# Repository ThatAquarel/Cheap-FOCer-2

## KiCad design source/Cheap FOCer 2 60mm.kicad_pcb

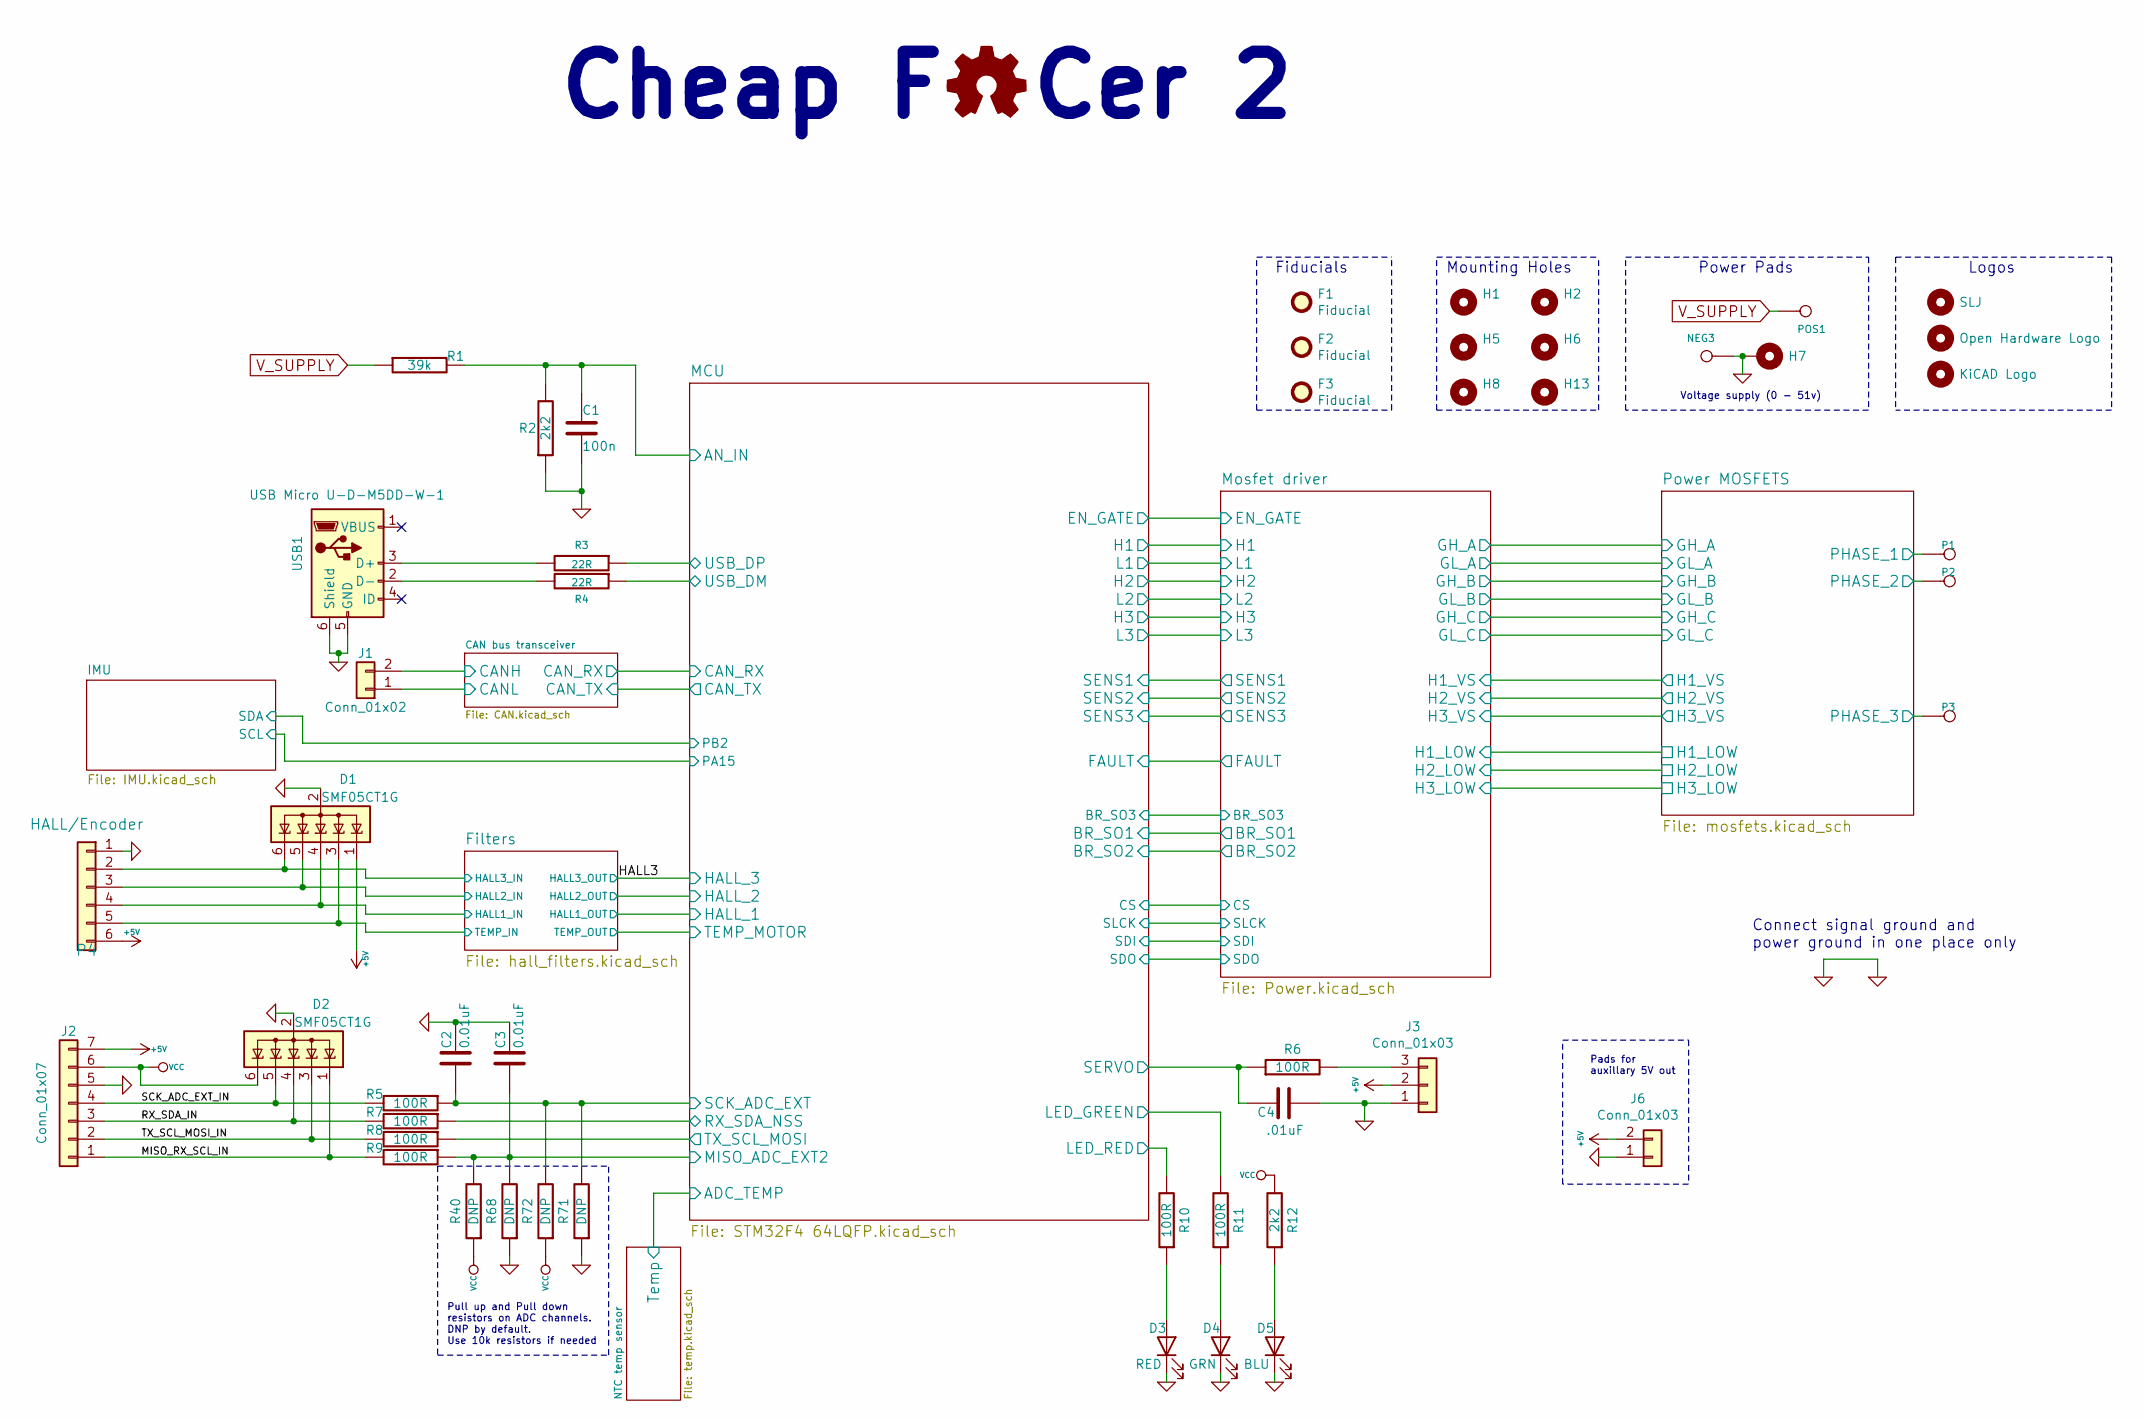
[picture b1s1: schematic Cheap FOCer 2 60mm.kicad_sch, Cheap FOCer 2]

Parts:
C1: 100n; C_0603_1608Metric
C2, C3: 0.01uF; C_0603_1608Metric
C4: .01uF; C_0603_1608Metric
D1, D2: SMF05CT1G; SOT-363_SC-70-6
D3: RED; LED_0603_1608Metric
D4: GRN; LED_0603_1608Metric
D5: BLU; LED_0603_1608Metric
F1, F2, F3: Fiducial; Fiducial_1mm_Dia_2mm_Outer
H1, H2, H5, H6, H7, H8, H13: MountingHole; MountingHole_3.2mm_M3_ISO14580_Pad
H3: SLJ; Sam_J
H4: Open Hardware Logo; OSHW-Logo2_9.8x8mm_SilkScreen
H9: KiCAD Logo; KiCad-Logo2_5mm_SilkScreen
J1: Conn_01x02; JST_PH_B2B-PH-K_1x02_P2.00mm_Vertical
J2: Conn_01x07; JST_PH_B7B-PH-K_1x07_P2.00mm_Vertical
J3: Conn_01x03; JST_PH_B3B-PH-K_1x03_P2.00mm_Vertical
J6: Conn_01x03; PinHeader_1x02_P2.54mm_Vertical
NEG3: MOTOR3; 1pin_4mm
P1, P2, P3: MOTOR1; 1pin_4mm
P4: HALL/Encoder; JST_PH_B6B-PH-K_1x06_P2.00mm_Vertical
POS1: POS; 1pin_4mm
R1: 39k; R_0603_1608Metric
R2, R12: 2k2; R_0603_1608Metric
R3, R4: 22R; R_0603_1608Metric
R5, R6, R7, R8, R9, R10, R11: 100R; R_0603_1608Metric
R40, R68, R71, R72: DNP; R_0603_1608Metric
USB1: USB Micro U-D-M5DD-W-1; USB_Micro-B_Wuerth_614105150721_Vertical

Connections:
+5V: D1.1 (K), J2.7, J3.2, J6.2, P4.6; also elsewhere on the board
/CAN bus transceiver/CANH: J1.2; also elsewhere on the board
/CAN bus transceiver/CANL: J1.1; also elsewhere on the board
/Filters/HALL1_IN: D1.4 (K), P4.4; also elsewhere on the board
/Filters/HALL2_IN: D1.5 (K), P4.3; also elsewhere on the board
/Filters/TEMP_IN: D1.3 (K), P4.5; also elsewhere on the board
/HALL3: D1.6 (K), P4.2; also elsewhere on the board
/MCU/AN_IN: C1.2, R1.2, R2.2; also elsewhere on the board
/MCU/LED_GREEN: R11.2; also elsewhere on the board
/MCU/LED_RED: R10.2; also elsewhere on the board
/MCU/MISO_ADC_EXT2: C3.2, R9.1, R40.2, R68.2; also elsewhere on the board
/MCU/RX_SDA_NSS: R7.1; also elsewhere on the board
/MCU/SCK_ADC_EXT: C2.2, R5.1, R71.2, R72.2; also elsewhere on the board
/MCU/SERVO: C4.2, R6.1; also elsewhere on the board
/MCU/TX_SCL_MOSI: R8.1; also elsewhere on the board
/MCU/USB_DM: R4.1; also elsewhere on the board
/MCU/USB_DP: R3.1; also elsewhere on the board
/MISO_RX_SCL_IN: D2.1 (K), J2.1, R9.2
/Mosfet driver/H1_VS: P1.1; also elsewhere on the board
/Mosfet driver/H2_VS: P2.1; also elsewhere on the board
/Mosfet driver/H3_VS: P3.1; also elsewhere on the board
/RX_SDA_IN: D2.4 (K), J2.3, R7.2
/SCK_ADC_EXT_IN: D2.5 (K), J2.4, R5.2
/TX_SCL_MOSI_IN: D2.3 (K), J2.2, R8.2
GND: C1.1, C2.1, C3.1, C4.1, D1.2 (A), D2.2 (A), D3.1 (K), D4.1 (K), D5.1 (K), H7.1, J2.5, J3.1, J6.1, NEG3.1, P4.1, R2.1, R68.1, R71.1, USB1.5 (GND), USB1.6 (Shield); also elsewhere on the board
unnamed: D3.2 (A), R10.1
unnamed: D4.2 (A), R11.1
unnamed: D5.2 (A), R12.1
unnamed: J3.3, R6.2
unnamed: R3.2, USB1.3 (D+)
unnamed: R4.2, USB1.2 (D-)
V_SUPPLY: POS1.1, R1.1; also elsewhere on the board

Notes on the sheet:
Mounting Holes
Pull up and Pull down resistors on ADC channels. DNP by default. Use 10k resistors if needed
Power Pads
Connect signal ground and power ground in one place only
Pads for auxillary 5V out
Logos
Fiducials
Voltage supply (0 - 51v)
Cheap F Cer 2

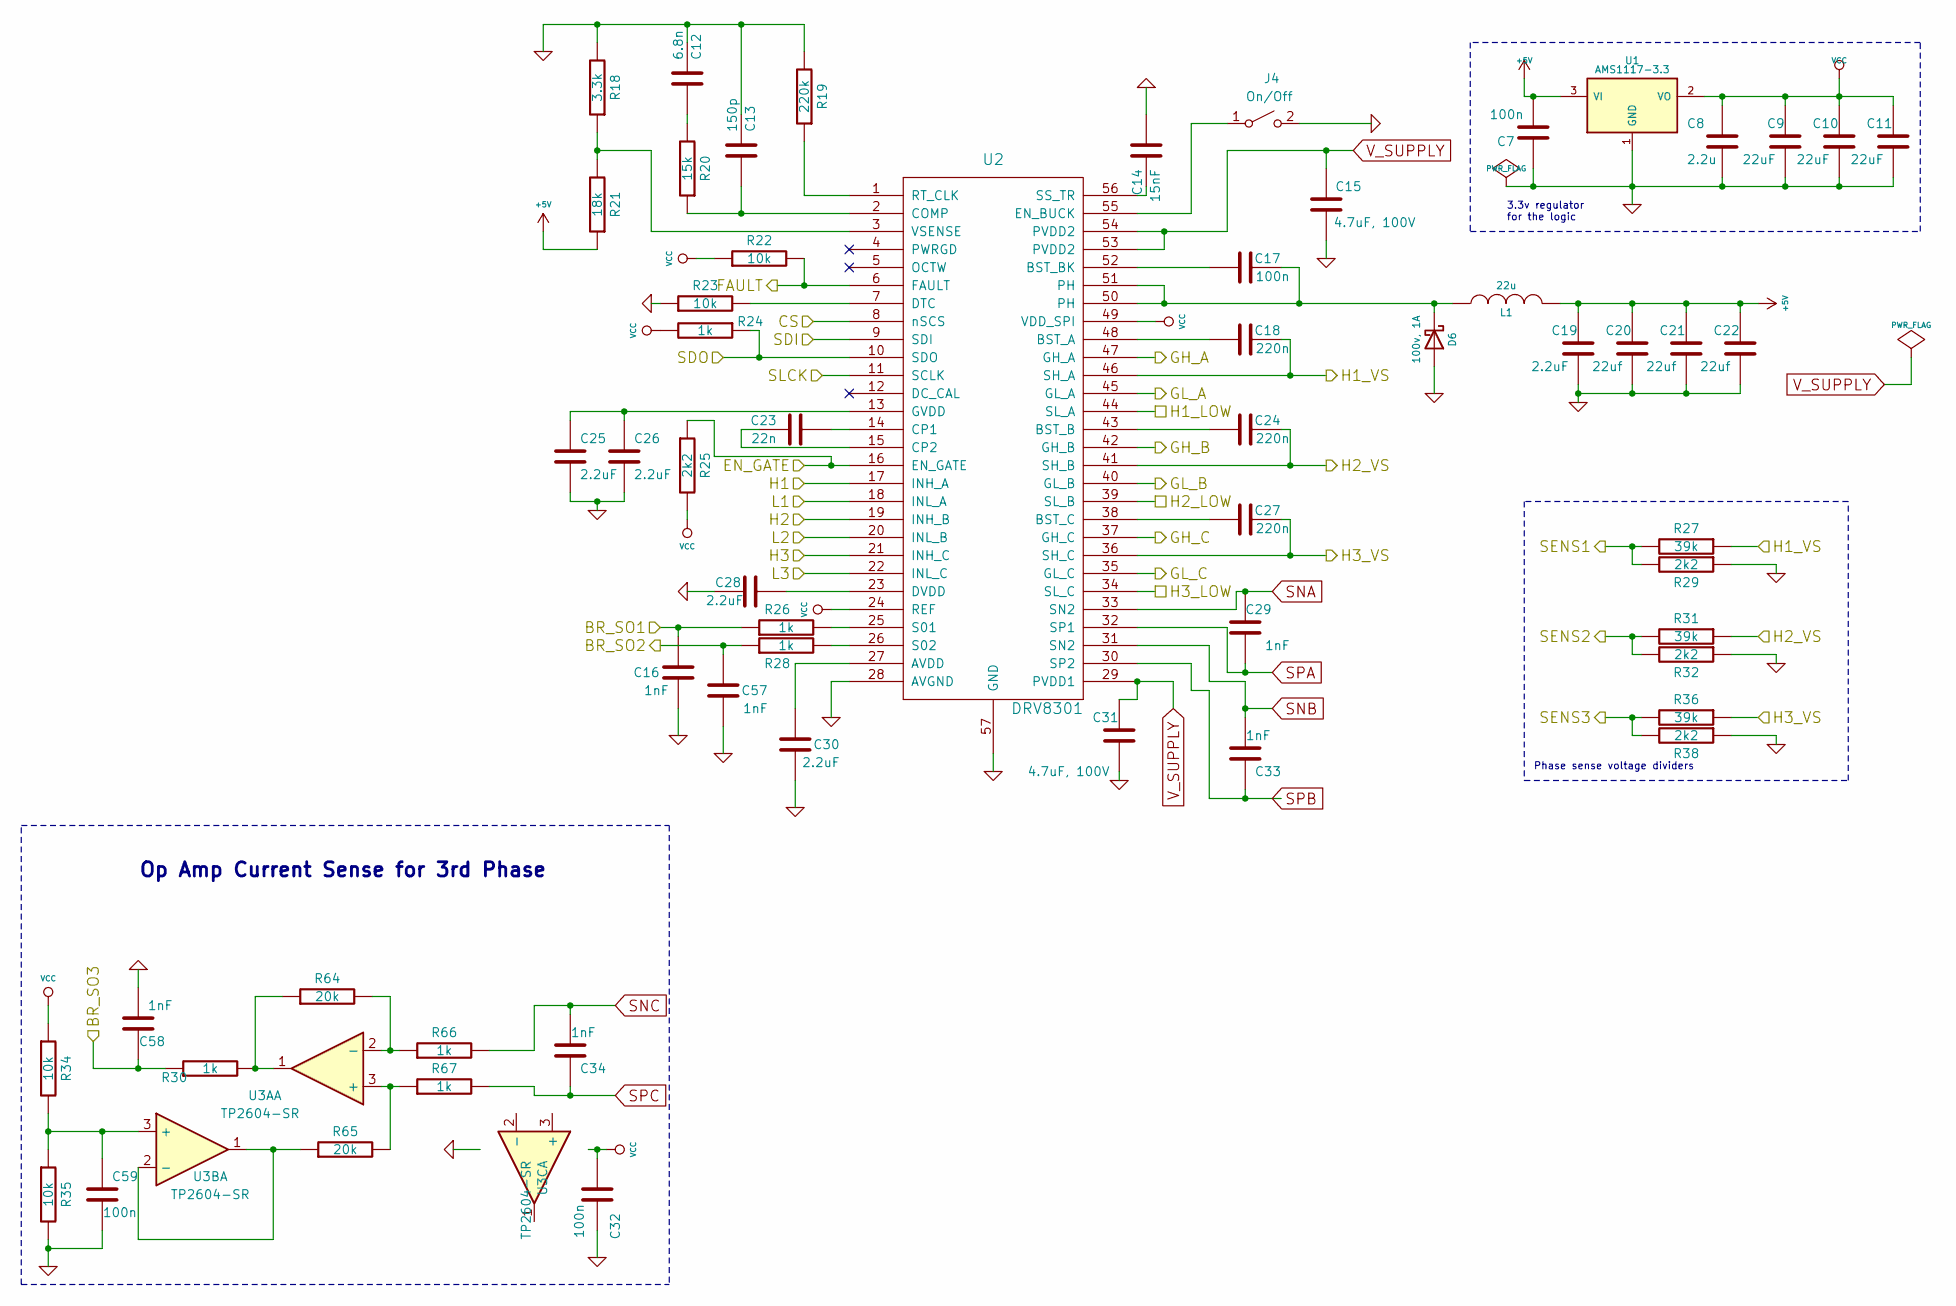
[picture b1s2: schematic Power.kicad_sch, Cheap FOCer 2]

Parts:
C7, C17, C32, C59: 100n; C_0603_1608Metric
C8: 2.2u; C_0603_1608Metric
C9, C10, C11: 22uF; C_0805_2012Metric
C12: 6.8n; C_0603_1608Metric
C13: 150p; C_0603_1608Metric
C14: 15nF; C_0603_1608Metric
C15, C31: 4.7uF, 100V; C_1210_3225Metric
C16, C29, C33, C34, C57, C58: 1nF; C_0603_1608Metric
C18, C24, C27: 220n; C_0603_1608Metric
C19, C25, C26, C28, C30: 2.2uF; C_0603_1608Metric
C20, C21, C22: 22uf; C_0805_2012Metric
C23: 22n; C_0603_1608Metric
D6: 100v, 1A; D_SMA
J4: On/Off; JST_PH_B2B-PH-K_1x02_P2.00mm_Vertical
L1: 22u; L_Taiyo-Yuden_NR-60xx_HandSoldering
R18: 3.3k; R_0603_1608Metric
R19: 220k; R_0603_1608Metric
R20: 15k; R_0603_1608Metric
R21: 18k; R_0603_1608Metric
R22, R23, R34, R35: 10k; R_0603_1608Metric
R24, R26, R28, R30, R66, R67: 1k; R_0603_1608Metric
R25, R29, R32, R38: 2k2; R_0603_1608Metric
R27, R31, R36: 39k; R_0603_1608Metric
R64, R65: 20k; R_0603_1608Metric
U1: AMS1117-3.3; SOT-223-3_TabPin2
U2: DRV8301; HTSSOP-56-1EP_6.1x14mm_P0.5mm_EP3.61x6.35mm
U3A, U3B, U3C: TP2604-SR; SOIC-8_3.9x4.9mm_P1.27mm

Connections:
+5V: C7.2, C19.2, C20.2, C21.2, C22.2, L1.2, R21.1, U1.3 (VI); also elsewhere on the board
/MCU/BR_SO1: C16.2, R26.1; also elsewhere on the board
/MCU/BR_SO2: C57.2, R28.1; also elsewhere on the board
/MCU/BR_SO3: C58.2, R30.1; also elsewhere on the board
/MCU/CS: U2.8 (nSCS); also elsewhere on the board
/MCU/EN_GATE: R25.1, U2.16 (EN_GATE); also elsewhere on the board
/MCU/FAULT: R22.2, U2.6 (FAULT); also elsewhere on the board
/MCU/H1: U2.17 (INH_A); also elsewhere on the board
/MCU/H2: U2.19 (INH_B); also elsewhere on the board
/MCU/H3: U2.21 (INH_C); also elsewhere on the board
/MCU/L1: U2.18 (INL_A); also elsewhere on the board
/MCU/L2: U2.20 (INL_B); also elsewhere on the board
/MCU/L3: U2.22 (INL_C); also elsewhere on the board
/MCU/SDI: U2.9 (SDI); also elsewhere on the board
/MCU/SDO: R24.1, U2.10 (SDO); also elsewhere on the board
/MCU/SENS1: R27.2, R29.2; also elsewhere on the board
/MCU/SENS2: R31.2, R32.2; also elsewhere on the board
/MCU/SENS3: R36.2, R38.2; also elsewhere on the board
/MCU/SLCK: U2.11 (SCLK); also elsewhere on the board
/Mosfet driver/GH_A: U2.47 (GH_A); also elsewhere on the board
/Mosfet driver/GH_B: U2.42 (GH_B); also elsewhere on the board
/Mosfet driver/GH_C: U2.37 (GH_C); also elsewhere on the board
/Mosfet driver/GL_A: U2.45 (GL_A); also elsewhere on the board
/Mosfet driver/GL_B: U2.40 (GL_B); also elsewhere on the board
/Mosfet driver/H1_VS: C18.2, R27.1, U2.46 (SH_A); also elsewhere on the board
/Mosfet driver/H2_LOW: U2.39 (SL_B); also elsewhere on the board
/Mosfet driver/H2_VS: C24.2, R31.1, U2.41 (SH_B); also elsewhere on the board
/Mosfet driver/H3_LOW: U2.34 (SL_C); also elsewhere on the board
/Mosfet driver/H3_VS: C27.2, R36.1, U2.36 (SH_C); also elsewhere on the board
GND: C7.1, C8.2, C9.1, C10.1, C11.1, C12.1, C13.1, C14.2, C15.1, C16.1, C19.1, C20.1, C21.1, C22.1, C25.2, C26.2, C28.2, C30.1, C31.1, C32.1, C57.1, C58.1, C59.2, D6.2 (A), J4.2 (B), R18.2, R19.2, R23.1, R29.1, R32.1, R35.2, R38.1, U1.1 (GND), U2.28 (AVGND), U2.57 (GND); also elsewhere on the board
unnamed: C12.2, R20.2
unnamed: C13.2, R20.1, U2.2 (COMP)
unnamed: C14.1, U2.56 (SS_TR)
unnamed: C17.1, U2.52 (BST_BK)
unnamed: C17.2, D6.1 (K), L1.1, U2.50 (PH), U2.51 (PH)
unnamed: C18.1, U2.48 (BST_A)
unnamed: C23.1, U2.15 (CP2)
unnamed: C23.2, U2.14 (CP1)
unnamed: C24.1, U2.43 (BST_B)
unnamed: C25.1, C26.1, U2.13 (GVDD)
unnamed: C27.1, U2.38 (BST_C)
unnamed: C28.1, U2.23 (DVDD)
unnamed: C30.2, U2.27 (AVDD)
unnamed 75: C59.1, R34.2, R35.1, U3B.3 (+); also elsewhere on the board
unnamed: J4.1 (A), U2.55 (EN_BUCK)
unnamed: R18.1, R21.2, U2.3 (VSENSE)
unnamed: R19.1, U2.1 (RT_CLK)
unnamed: R23.2, U2.7 (DTC)
unnamed: R26.2, U2.25 (S01)
unnamed: R28.2, U2.26 (S02)
unnamed 92: R30.2, R64.1, U3A.1; also elsewhere on the board
unnamed 93: R64.2, R66.1, U3A.2 (-); also elsewhere on the board
unnamed 94: R65.1, U3B.1, U3B.2 (-); also elsewhere on the board
unnamed 95: R65.2, R67.1, U3A.3 (+); also elsewhere on the board
SNA: C29.2, U2.33 (SN2); also elsewhere on the board
SNB: C33.1, U2.31 (SN2); also elsewhere on the board
SNC: C34.1, R66.2; also elsewhere on the board
SPA: C29.1, U2.32 (SP1); also elsewhere on the board
SPB: C33.2, U2.30 (SP2); also elsewhere on the board
SPC: C34.2, R67.2; also elsewhere on the board
V_SUPPLY: C15.2, C31.2, U2.29 (PVDD1), U2.53 (PVDD2), U2.54 (PVDD2); also elsewhere on the board

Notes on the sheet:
Phase sense voltage dividers
3.3v regulator for the logic
Op Amp Current Sense for 3rd Phase

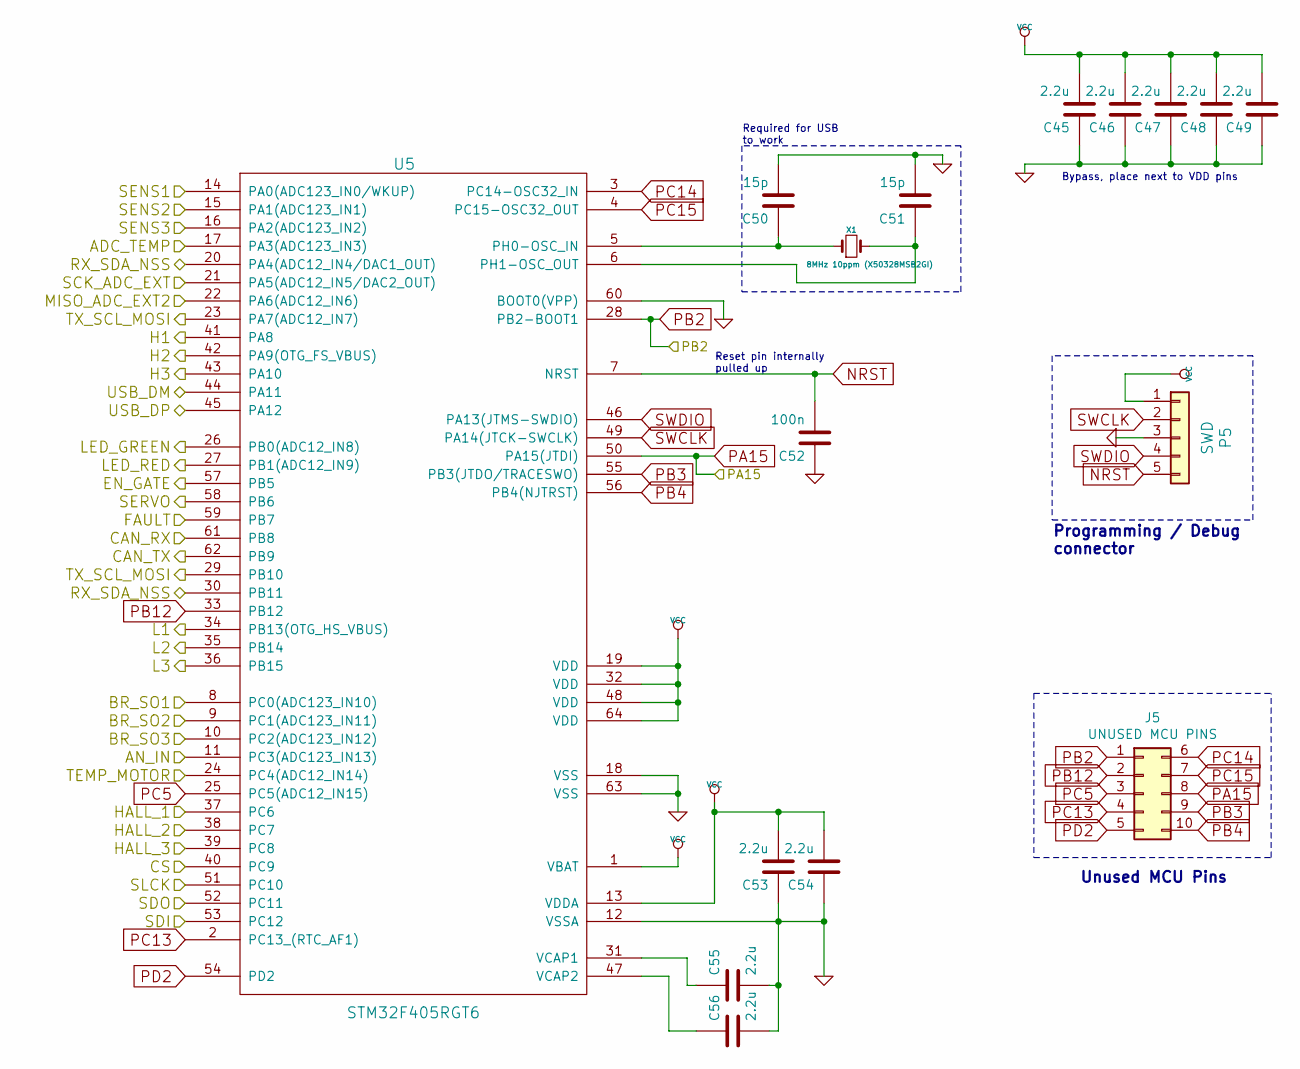
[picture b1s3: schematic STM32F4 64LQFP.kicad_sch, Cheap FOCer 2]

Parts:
C45, C46, C47, C48, C49, C53, C54, C55, C56: 2.2u; C_0603_1608Metric
C50, C51: 15p; C_0603_1608Metric
C52: 100n; C_0603_1608Metric
J5: UNUSED MCU PINS; PinHeader_2x05_P2.00mm_Vertical
P5: SWD; PinHeader_1x05_P2.54mm_Vertical
U5: STM32F405RGT6; LQFP-64_10x10mm_P0.5mm
X1: 8MHz 10ppm (X50328MSB2GI); Crystal_SMD_5032-2Pin_5.0x3.2mm; mfg# ABM3B-8.0-10-1UT

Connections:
/CAN bus transceiver/CAN_RX: U5.61 (PB8); also elsewhere on the board
/CAN bus transceiver/CAN_TX: U5.62 (PB9); also elsewhere on the board
/Filters/HALL1_IN: U5.37 (PC6); also elsewhere on the board
/Filters/HALL2_IN: U5.38 (PC7); also elsewhere on the board
/Filters/TEMP_IN: U5.24 (PC4(ADC12_IN14)); also elsewhere on the board
/HALL3: U5.39 (PC8); also elsewhere on the board
/MCU/ADC_TEMP: U5.17 (PA3(ADC123_IN3)); also elsewhere on the board
/MCU/AN_IN: U5.11 (PC3(ADC123_IN13)); also elsewhere on the board
/MCU/BR_SO1: U5.8 (PC0(ADC123_IN10)); also elsewhere on the board
/MCU/BR_SO2: U5.9 (PC1(ADC123_IN11)); also elsewhere on the board
/MCU/BR_SO3: U5.10 (PC2(ADC123_IN12)); also elsewhere on the board
/MCU/CS: U5.40 (PC9); also elsewhere on the board
/MCU/EN_GATE: U5.57 (PB5); also elsewhere on the board
/MCU/FAULT: U5.59 (PB7); also elsewhere on the board
/MCU/H1: U5.41 (PA8); also elsewhere on the board
/MCU/H2: U5.42 (PA9(OTG_FS_VBUS)); also elsewhere on the board
/MCU/H3: U5.43 (PA10); also elsewhere on the board
/MCU/L1: U5.34 (PB13(OTG_HS_VBUS)); also elsewhere on the board
/MCU/L2: U5.35 (PB14); also elsewhere on the board
/MCU/L3: U5.36 (PB15); also elsewhere on the board
/MCU/LED_GREEN: U5.26 (PB0(ADC12_IN8)); also elsewhere on the board
/MCU/LED_RED: U5.27 (PB1(ADC12_IN9)); also elsewhere on the board
/MCU/MISO_ADC_EXT2: U5.22 (PA6(ADC12_IN6)); also elsewhere on the board
/MCU/RX_SDA_NSS: U5.20 (PA4(ADC12_IN4/DAC1_OUT)), U5.30 (PB11); also elsewhere on the board
/MCU/SCK_ADC_EXT: U5.21 (PA5(ADC12_IN5/DAC2_OUT)); also elsewhere on the board
/MCU/SDI: U5.53 (PC12); also elsewhere on the board
/MCU/SDO: U5.52 (PC11); also elsewhere on the board
/MCU/SENS1: U5.14 (PA0(ADC123_IN0/WKUP)); also elsewhere on the board
/MCU/SENS2: U5.15 (PA1(ADC123_IN1)); also elsewhere on the board
/MCU/SENS3: U5.16 (PA2(ADC123_IN2)); also elsewhere on the board
/MCU/SERVO: U5.58 (PB6); also elsewhere on the board
/MCU/SLCK: U5.51 (PC10); also elsewhere on the board
/MCU/TX_SCL_MOSI: U5.23 (PA7(ADC12_IN7)), U5.29 (PB10); also elsewhere on the board
/MCU/USB_DM: U5.44 (PA11); also elsewhere on the board
/MCU/USB_DP: U5.45 (PA12); also elsewhere on the board
GND: C45.1, C46.1, C47.1, C48.1, C49.1, C50.2, C51.2, C52.1, C53.1, C54.1, C55.2, C56.2, P5.3, U5.12 (VSSA), U5.18 (VSS), U5.60 (BOOT0(VPP)), U5.63 (VSS); also elsewhere on the board
NRST: C52.2, P5.5, U5.7 (NRST)
unnamed: C50.1, U5.5 (PH0-OSC_IN), X1.1
unnamed: C51.1, U5.6 (PH1-OSC_OUT), X1.2
unnamed: C55.1, U5.31 (VCAP1)
unnamed: C56.1, U5.47 (VCAP2)
PB3: J5.9, U5.55 (PB3(JTDO/TRACESWO))
PB4: J5.10, U5.56 (PB4(NJTRST))
PB12: J5.2, U5.33 (PB12)
PC5: J5.3, U5.25 (PC5(ADC12_IN15))
PC13: J5.4, U5.2 (PC13_(RTC_AF1))
PC14: J5.6, U5.3 (PC14-OSC32_IN)
PC15: J5.7, U5.4 (PC15-OSC32_OUT)
PD2: J5.5, U5.54 (PD2)
SWCLK: P5.2, U5.49 (PA14(JTCK-SWCLK))
SWDIO: P5.4, U5.46 (PA13(JTMS-SWDIO))

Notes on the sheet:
Bypass, place next to VDD pins
Programming / Debug connector
Reset pin internally pulled up
Unused MCU Pins
Required for USB to work

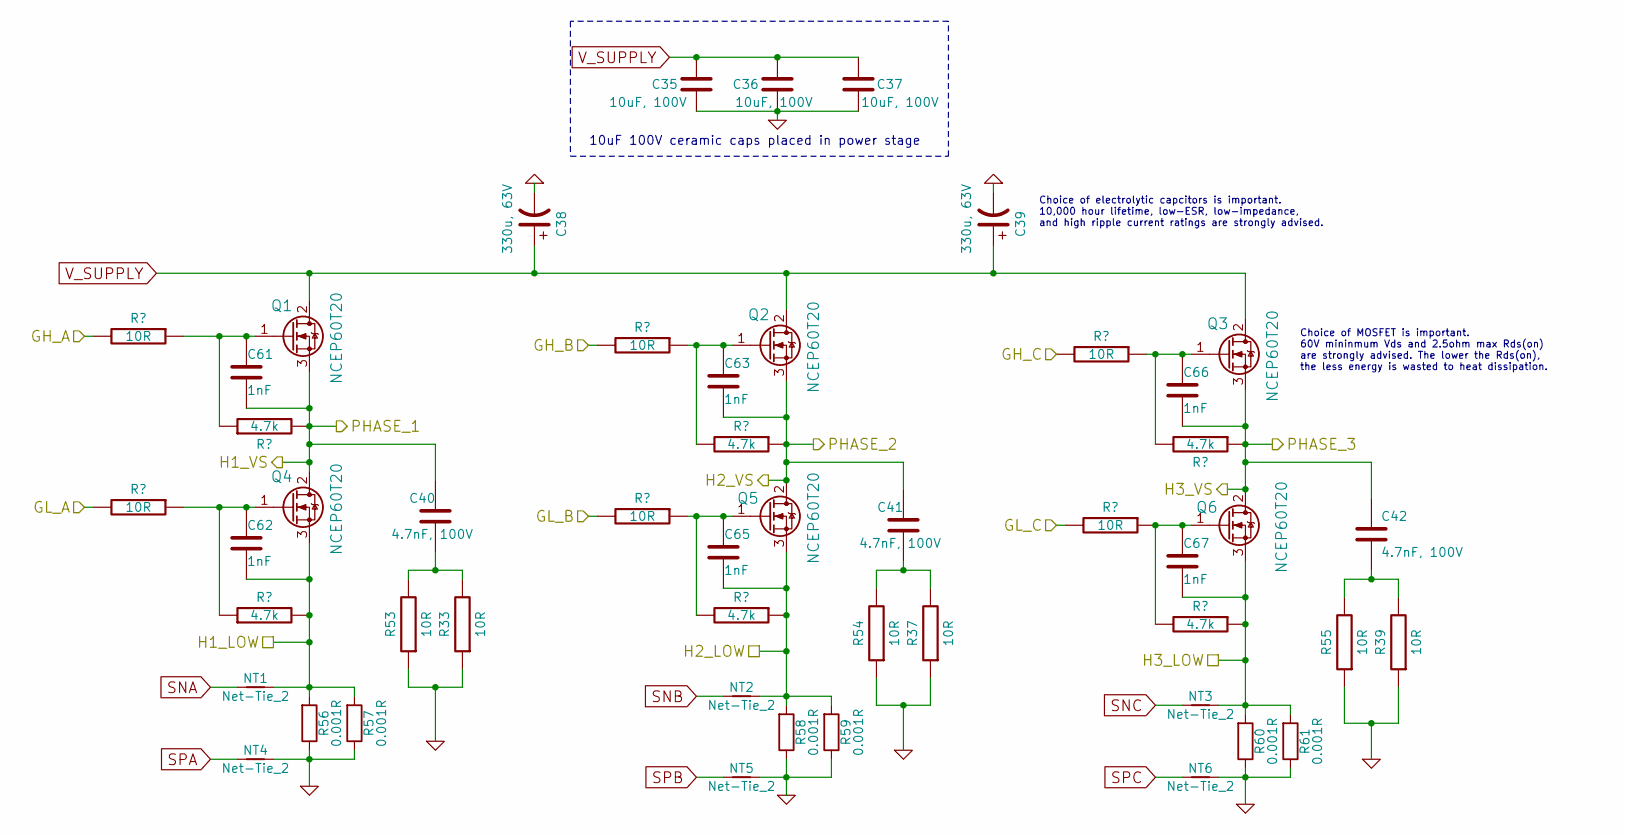
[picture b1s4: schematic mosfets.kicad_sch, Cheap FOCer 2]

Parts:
C35, C36, C37: 10uF, 100V; C_2220_5650Metric_Pad1.97x5.40mm_HandSolder
C38, C39: 330u, 63V; CP_10x20mm_hor_with_model_brd_edge
C40, C41, C42: 4.7nF, 100V; C_0805_2012Metric
C61, C62, C63, C65, C66, C67: 1nF; C_0603_1608Metric
NT1, NT2, NT3, NT4, NT5, NT6: Net-Tie_2; NetTie-2_SMD_Pad0.5mm
Q1, Q2, Q3, Q4, Q5, Q6: NCEP60T20; TO-220-3_Horizontal_TabUp_no_hole
R33, R37, R39, R41, R42, R43, R47, R48, R49, R53, R54, R55: 10R; R_0805_2012Metric
R44, R45, R46, R50, R51, R52: 4.7k; R_0603_1608Metric
R56, R57, R58, R59, R60, R61: 0.001R; R_2512_Yageo_big_pads

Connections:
/Mosfet driver/GH_A: R41.2; also elsewhere on the board
/Mosfet driver/GH_B: R42.2; also elsewhere on the board
/Mosfet driver/GH_C: R43.2; also elsewhere on the board
/Mosfet driver/GL_A: R47.2; also elsewhere on the board
/Mosfet driver/GL_B: R48.2; also elsewhere on the board
/Mosfet driver/H1_VS: C40.1, C61.2, Q1.3 (S), Q4.2 (D), R44.2; also elsewhere on the board
/Mosfet driver/H2_LOW: C65.2, NT2.2, Q5.3 (S), R51.1, R58.2, R59.2; also elsewhere on the board
/Mosfet driver/H2_VS: C41.1, C63.2, Q2.3 (S), Q5.2 (D), R45.1; also elsewhere on the board
/Mosfet driver/H3_LOW: C67.2, NT3.2, Q6.3 (S), R52.1, R60.2, R61.2; also elsewhere on the board
/Mosfet driver/H3_VS: C42.1, C66.2, Q3.3 (S), Q6.2 (D), R46.1; also elsewhere on the board
GND: C35.1, C36.1, C37.1, C38.2, C39.2, NT4.2, NT5.2, NT6.2, R33.1, R37.1, R39.1, R53.1, R54.1, R55.1, R56.1, R57.1, R58.1, R59.1, R60.1, R61.1; also elsewhere on the board
unnamed: C40.2, R33.2, R53.2
unnamed: C41.2, R37.2, R54.2
unnamed: C42.2, R39.2, R55.2
unnamed: C61.1, Q1.1 (G), R41.1, R44.1
unnamed: C63.1, Q2.1 (G), R42.1, R45.2
unnamed: C65.1, Q5.1 (G), R48.1, R51.2
unnamed: C66.1, Q3.1 (G), R43.1, R46.2
SNA: NT1.1; also elsewhere on the board
SNB: NT2.1; also elsewhere on the board
SNC: NT3.1; also elsewhere on the board
SPA: NT4.1; also elsewhere on the board
SPB: NT5.1; also elsewhere on the board
SPC: NT6.1; also elsewhere on the board
V_SUPPLY: C35.2, C36.2, C37.2, C38.1, C39.1, Q1.2 (D), Q2.2 (D), Q3.2 (D); also elsewhere on the board

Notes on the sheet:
10uF 100V ceramic caps placed in power stage
Choice of MOSFET is important. 60V mininmum Vds and 2.5ohm max Rds(on) are strongly advised. The lower the Rds(on), the less energy is wasted to heat dissipation.
Choice of electrolytic capcitors is important. 10,000 hour lifetime, low-ESR, low-impedance, and high ripple current ratings are strongly advised.

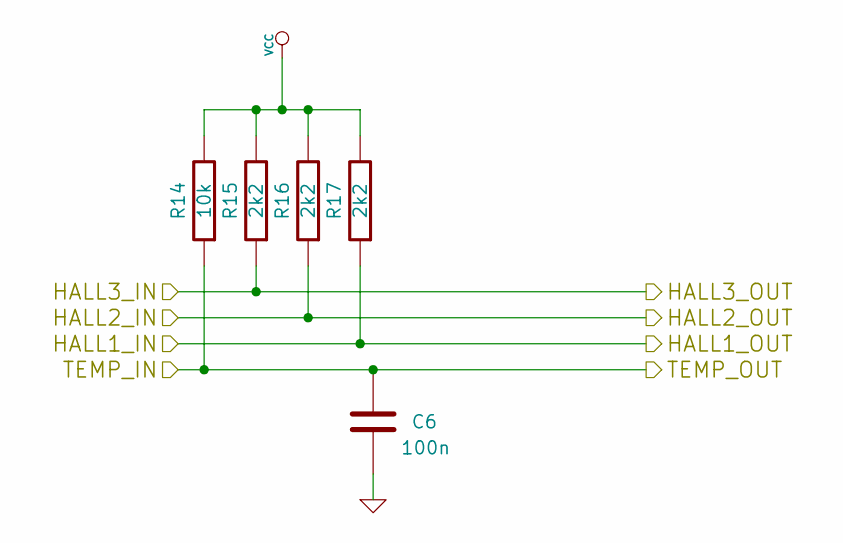
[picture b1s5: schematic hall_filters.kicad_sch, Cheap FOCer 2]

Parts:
C6: 100n; C_0603_1608Metric
R14: 10k; R_0603_1608Metric
R15, R16, R17: 2k2; R_0603_1608Metric

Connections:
/Filters/HALL1_IN: R17.1; also elsewhere on the board
/Filters/HALL2_IN: R16.1; also elsewhere on the board
/Filters/TEMP_IN: C6.2, R14.1; also elsewhere on the board
/HALL3: R15.1; also elsewhere on the board
GND: C6.1; also elsewhere on the board

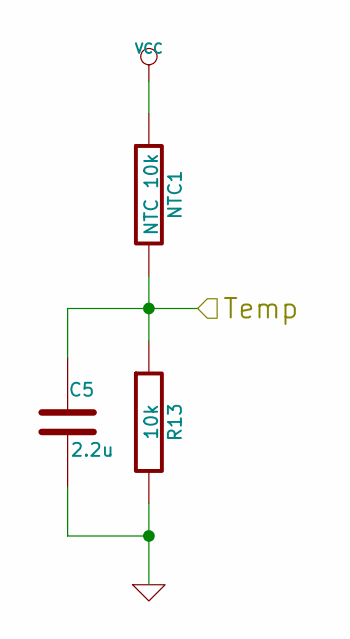
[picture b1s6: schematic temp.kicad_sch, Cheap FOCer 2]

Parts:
C5: 2.2u; C_0603_1608Metric
NTC1: NTC 10k; R_0603_1608Metric
R13: 10k; R_0603_1608Metric

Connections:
/MCU/ADC_TEMP: C5.1, NTC1.2, R13.1; also elsewhere on the board
GND: C5.2, R13.2; also elsewhere on the board

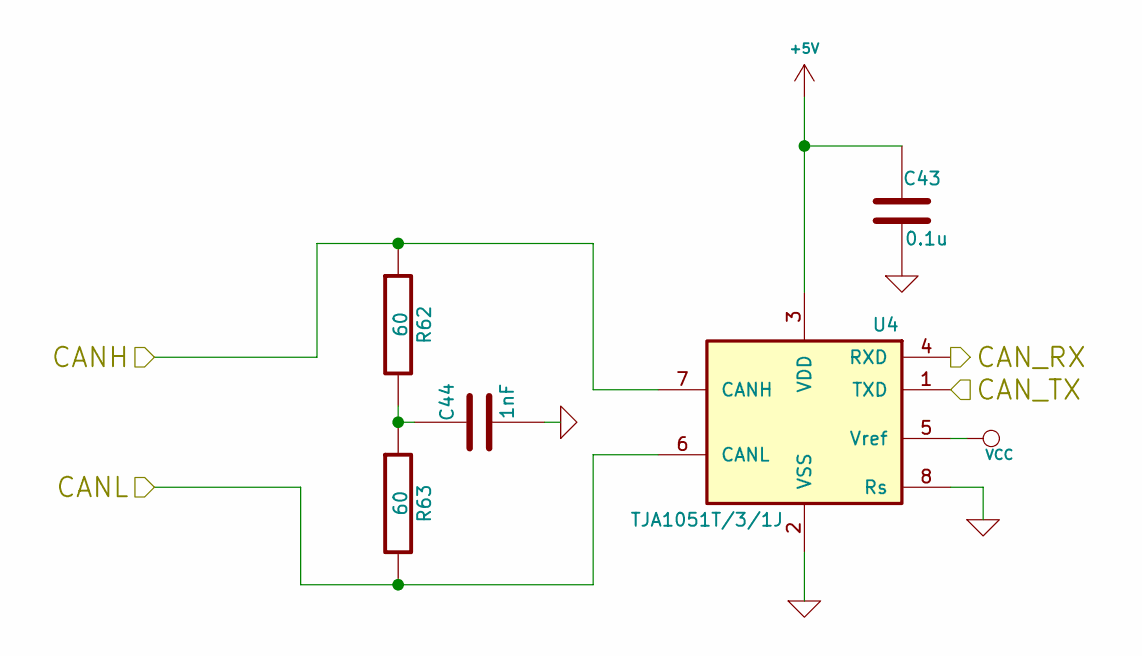
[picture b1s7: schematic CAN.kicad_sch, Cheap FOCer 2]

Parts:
C43: 0.1u; C_0603_1608Metric
C44: 1nF; C_0603_1608Metric
R62, R63: 60; R_0603_1608Metric
U4: TJA1051T/3/1J; SOIC-8_3.9x4.9mm_P1.27mm

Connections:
+5V: C43.1, U4.3 (VDD); also elsewhere on the board
/CAN bus transceiver/CANH: R62.1, U4.7 (CANH); also elsewhere on the board
/CAN bus transceiver/CANL: R63.2, U4.6 (CANL); also elsewhere on the board
/CAN bus transceiver/CAN_RX: U4.4 (RXD); also elsewhere on the board
/CAN bus transceiver/CAN_TX: U4.1 (TXD); also elsewhere on the board
GND: C43.2, C44.2, U4.2 (VSS), U4.8 (Rs); also elsewhere on the board
unnamed: C44.1, R62.2, R63.1

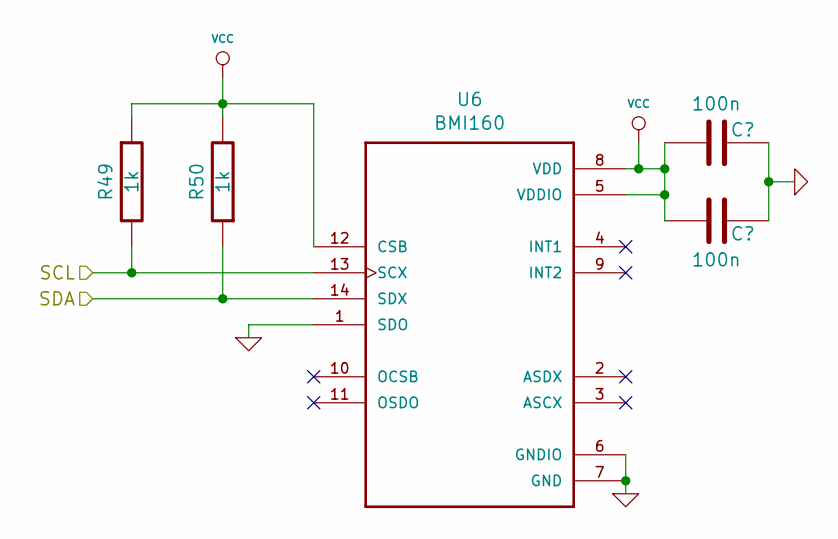
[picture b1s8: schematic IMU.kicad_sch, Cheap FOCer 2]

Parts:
C60, C64: 100n; C_0603_1608Metric
R49, R50: 1k; R_0603_1608Metric
U6: BMI160; Bosch_LGA-14_3x2.5mm_P0.5mm

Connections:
GND: C60.1, C64.1, U6.1 (SDO), U6.6 (GNDIO), U6.7 (GND); also elsewhere on the board

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
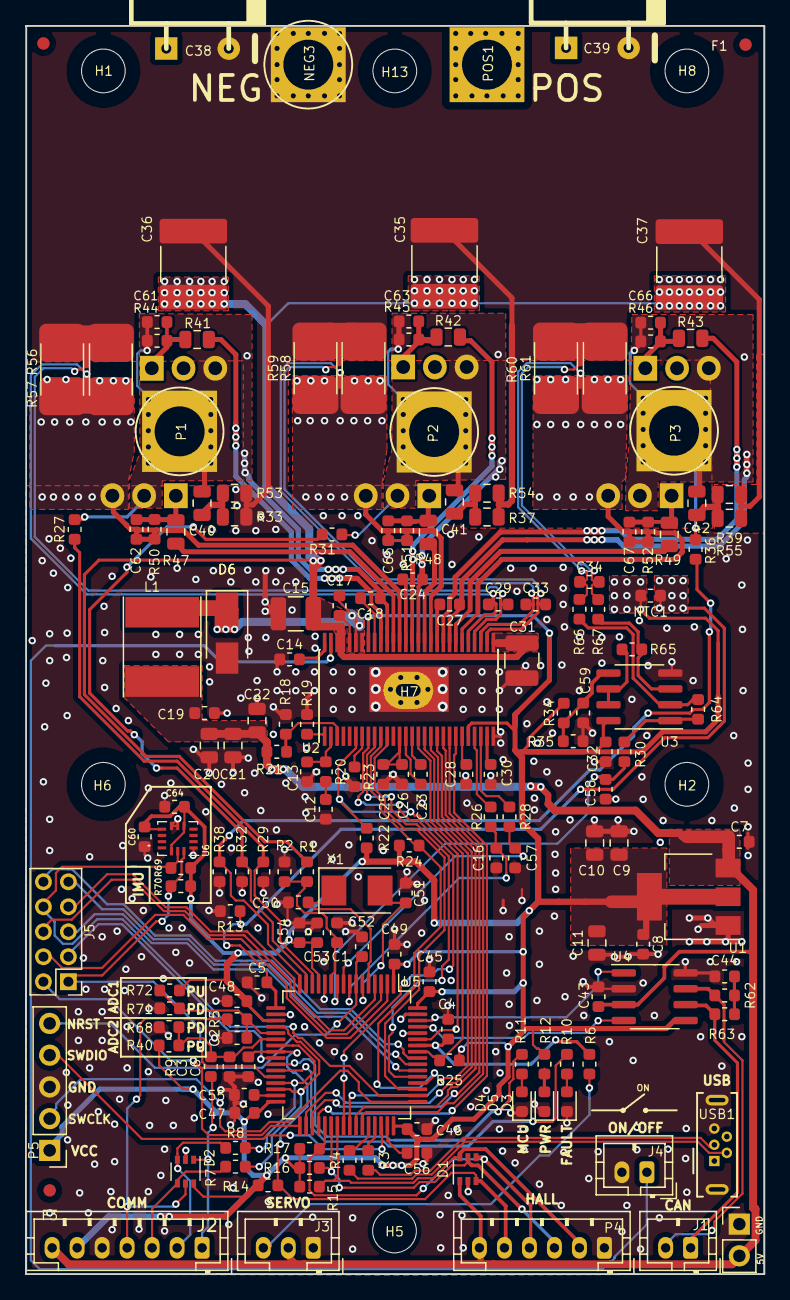
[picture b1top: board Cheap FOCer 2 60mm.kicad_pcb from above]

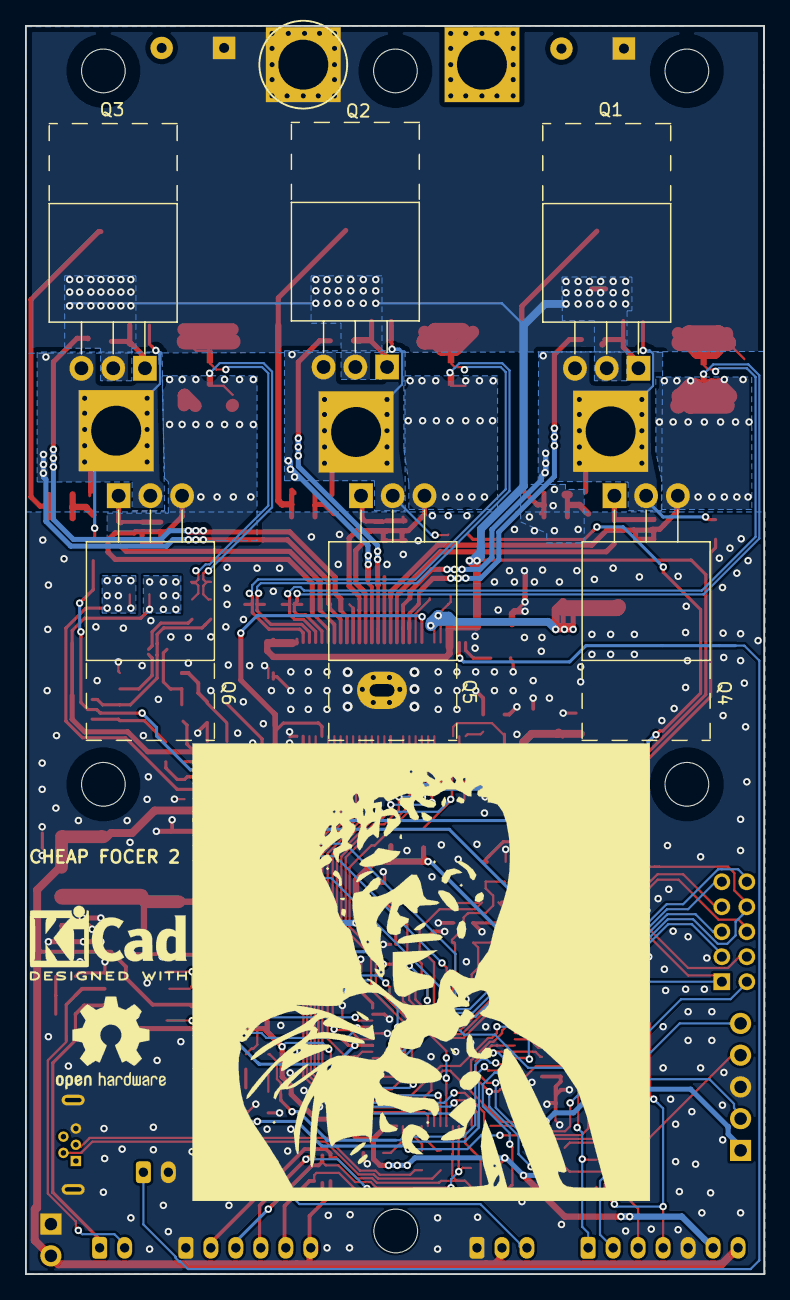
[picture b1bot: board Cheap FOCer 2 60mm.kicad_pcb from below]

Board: 2 copper layers, 59.1 x 99.9 mm, 193 parts (10 on the bottom side), 120 nets.

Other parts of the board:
R69, R70: 1k; R_0603_1608Metric
U3: TP2604-SR; SOIC-8_3.9x4.9mm_P1.27mm

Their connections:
GND: U3.4; also elsewhere on the board
unnamed 75: U3.5; also elsewhere on the board
unnamed 92: U3.1; also elsewhere on the board
unnamed 93: U3.2; also elsewhere on the board
unnamed 94: U3.6, U3.7; also elsewhere on the board
unnamed 95: U3.3; also elsewhere on the board

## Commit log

2024-12-27 renew kicad to v8
